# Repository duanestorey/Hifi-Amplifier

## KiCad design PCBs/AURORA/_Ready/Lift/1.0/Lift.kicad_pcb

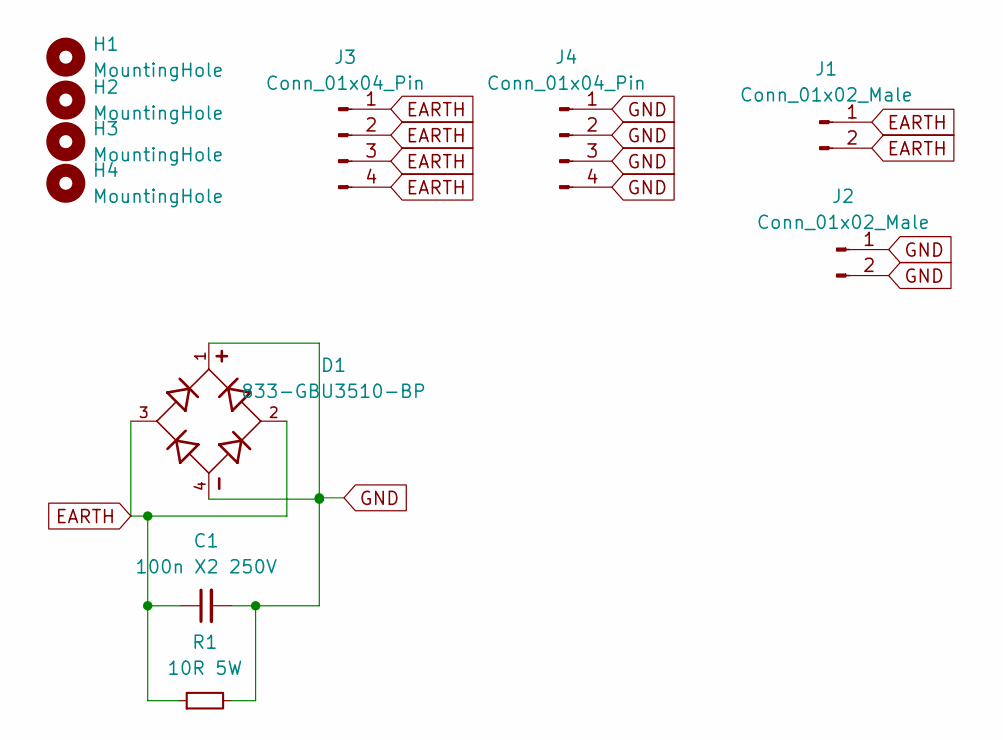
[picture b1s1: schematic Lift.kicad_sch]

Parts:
C1: 100n X2 250V; C_Rect_L18.0mm_W5.0mm_P15.00mm_FKS3_FKP3; Mouser 871-B32922X2104K000
D1: 833-GBU3510-BP; Diode_Bridge_Vishay_GBU; Mouser 833-GBU3510-BP
H1, H2, H3, H4: MountingHole; MountingHole_3.2mm_M3_DIN965_Pad_TopOnly
J1, J2: Conn_01x02_Male; JST_VH_B2P-VH-B_1x02_P3.96mm_Vertical
J3, J4: Conn_01x04_Pin; TerminalBlock_Phoenix_PT-1,5-4-3.5-H_1x04_P3.50mm_Horizontal
R1: 10R 5W; R_Axial_DIN0617_L17.0mm_D6.0mm_P25.40mm_Horizontal; Mouser 594-AC05W10R00J

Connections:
EARTH: C1.1, D1.2, D1.3, J1.1, J1.2, J3.1, J3.2, J3.3, J3.4, R1.1
GND: C1.2, D1.1, D1.4, J2.1, J2.2, J4.1, J4.2, J4.3, J4.4, R1.2

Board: 2 copper layers, 11 parts (0 on the bottom side), 2 nets, no tracks yet.

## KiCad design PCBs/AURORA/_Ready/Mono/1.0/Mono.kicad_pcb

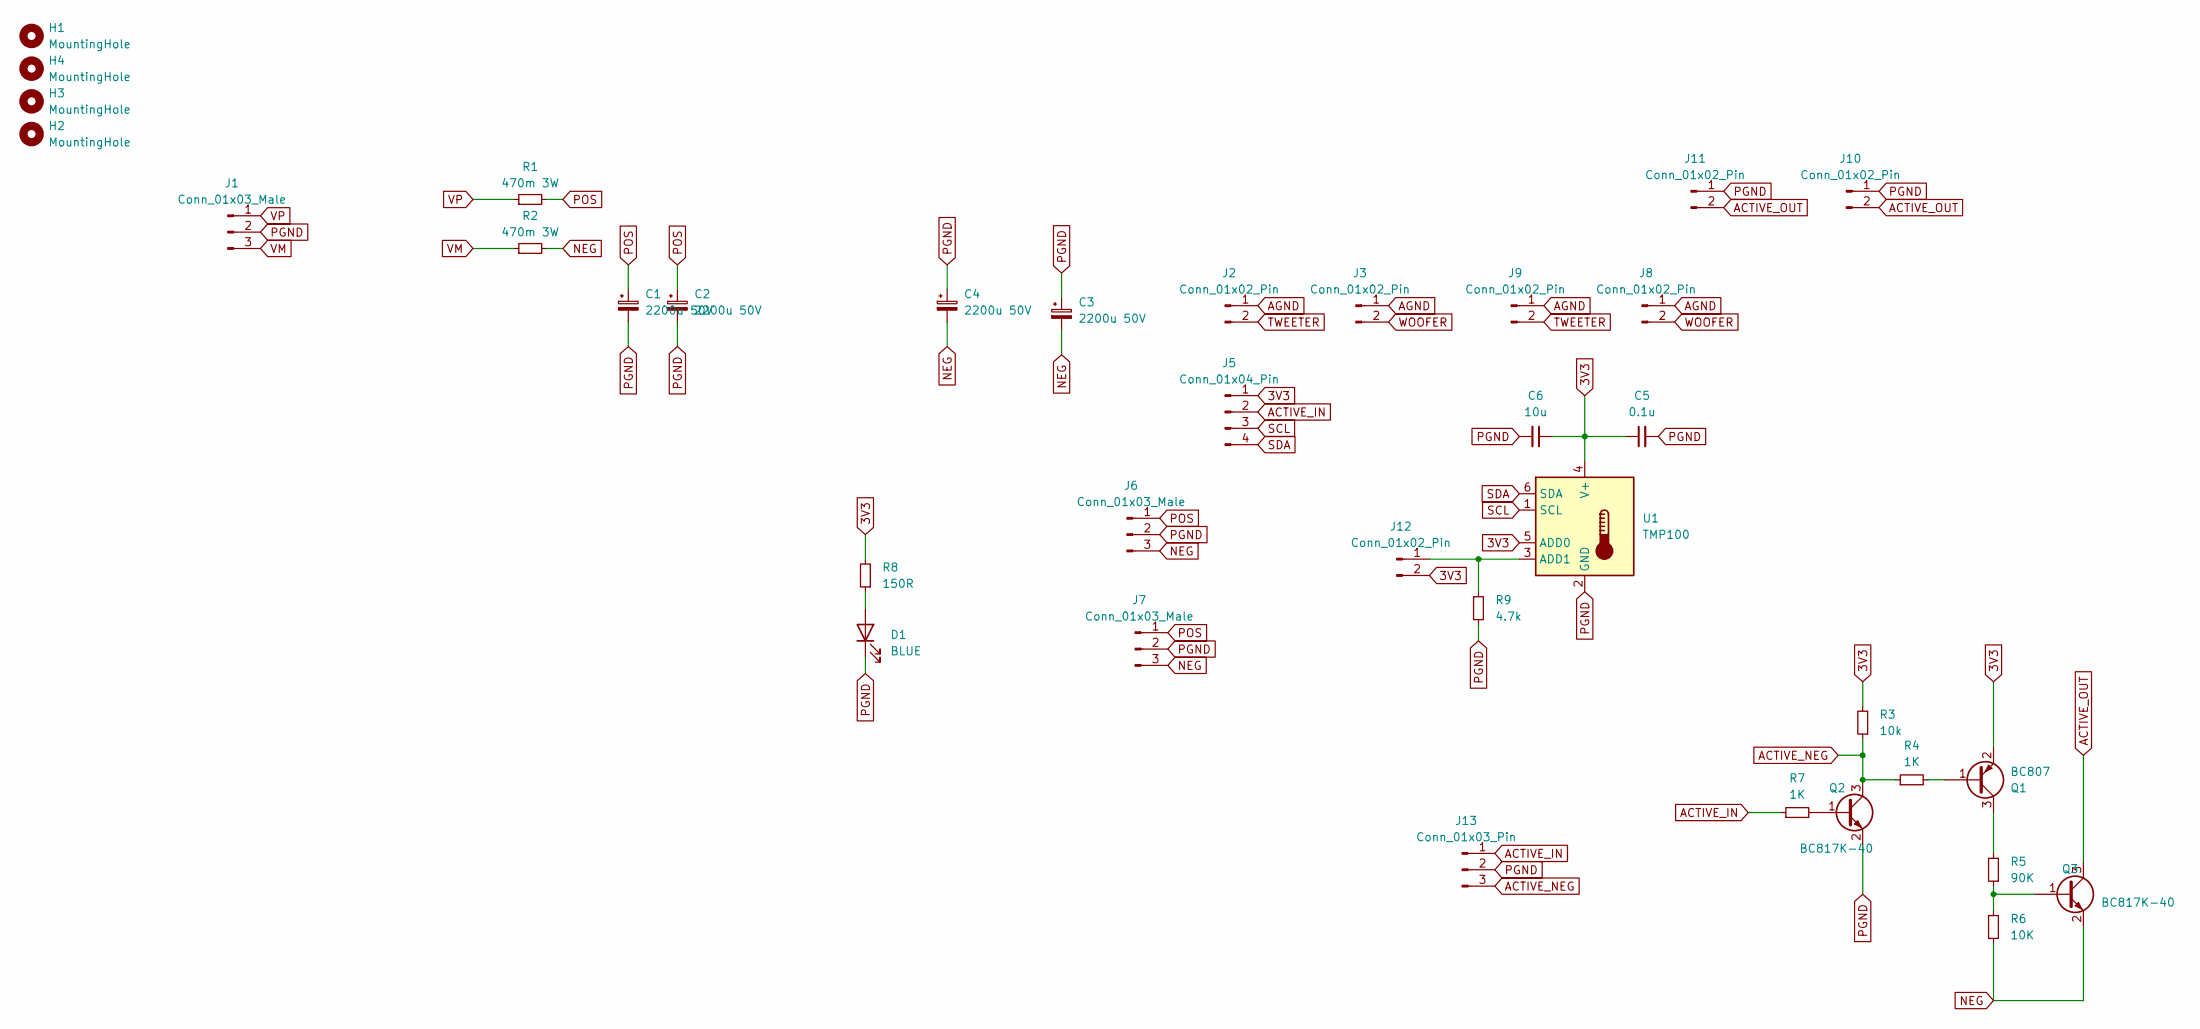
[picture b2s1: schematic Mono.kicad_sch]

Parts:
C1, C2, C3, C4: 2200u 50V; CP_Radial_D16.0mm_P7.50mm; Mouser 80-ESH228M050AM3AA
C5: 0.1u; C_0805_2012Metric_Pad1.18x1.45mm_HandSolder
C6: 10u; C_1206_3216Metric_Pad1.33x1.80mm_HandSolder
D1: BLUE; LED_0603_1608Metric_Pad1.05x0.95mm_HandSolder
H1, H2, H3, H4: MountingHole; MountingHole_3.2mm_M3_DIN965_Pad_TopOnly
J1, J6, J7: Conn_01x03_Male; JST_VH_B3P-VH-B_1x03_P3.96mm_Vertical
J2, J3, J8, J9, J10, J11: Conn_01x02_Pin; JST_PH_B2B-PH-K_1x02_P2.00mm_Vertical
J5: Conn_01x04_Pin; JST_PH_B4B-PH-K_1x04_P2.00mm_Vertical
J12: Conn_01x02_Pin; PinHeader_1x02_P2.54mm_Vertical
J13: Conn_01x03_Pin; JST_PH_B3B-PH-K_1x03_P2.00mm_Vertical
Q1: BC807; TSOT-23; Mouser 637-BC807-16
Q2, Q3: BC817K-40; TSOT-23; Mouser 637-BC817K-40
R1, R2: 470m 3W; R_1218_3246Metric_Pad1.22x4.75mm_HandSolder; Mouser RLW73PA3FR47TDF
R3: 10k; R_0603_1608Metric_Pad0.98x0.95mm_HandSolder
R4, R7: 1K; R_0603_1608Metric_Pad0.98x0.95mm_HandSolder
R5: 90K; R_0603_1608Metric_Pad0.98x0.95mm_HandSolder
R6: 10K; R_0603_1608Metric_Pad0.98x0.95mm_HandSolder
R8: 150R; R_0603_1608Metric_Pad0.98x0.95mm_HandSolder
R9: 4.7k; R_0603_1608Metric_Pad0.98x0.95mm_HandSolder
U1: TMP100; SOT-23-6

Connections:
3V3: C5.1, C6.1, J5.1, J12.2, Q1.2 (E), R3.2, R8.2, U1.4 (V+), U1.5 (ADD0)
ACTIVE_IN: J5.2, J13.1, R7.1
ACTIVE_NEG: J13.3, Q2.3 (C), R3.1, R4.1
ACTIVE_OUT: J10.2, J11.2, Q3.3 (C)
AGND: J2.1, J3.1, J8.1, J9.1
NEG: C3.2, C4.2, J6.3, J7.3, Q3.2 (E), R2.2, R6.1
unnamed: D1.2 (A), R8.1
unnamed: J12.1, R9.1, U1.3 (ADD1)
unnamed: Q1.1 (B), R4.2
unnamed: Q1.3 (C), R5.2
unnamed: Q2.1 (B), R7.2
unnamed: Q3.1 (B), R5.1, R6.2
PGND: C1.2, C2.2, C3.1, C4.1, C5.2, C6.2, D1.1 (K), J1.2, J6.2, J7.2, J10.1, J11.1, J13.2, Q2.2 (E), R9.2, U1.2 (GND)
POS: C1.1, C2.1, J6.1, J7.1, R1.2
SCL: J5.3, U1.1 (SCL)
SDA: J5.4, U1.6 (SDA)
TWEETER: J2.2, J9.2
VM: J1.3, R2.1
VP: J1.1, R1.1
WOOFER: J3.2, J8.2

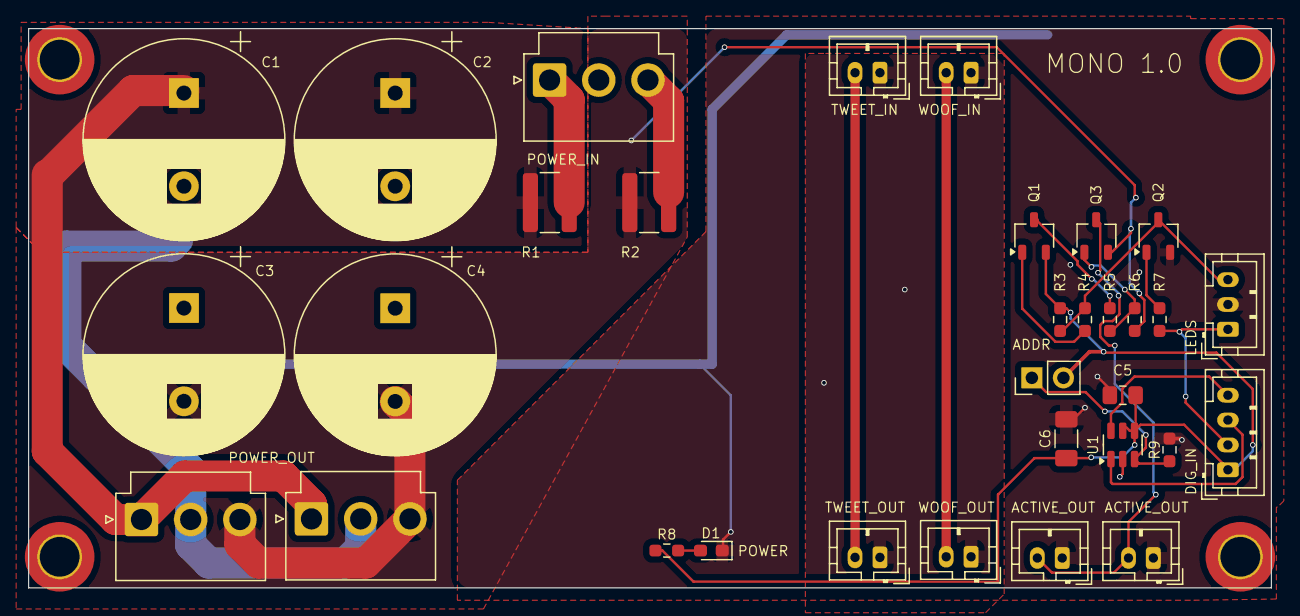
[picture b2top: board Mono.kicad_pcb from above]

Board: 2 copper layers, 100.0 x 45.0 mm, 36 parts (0 on the bottom side), 20 nets.

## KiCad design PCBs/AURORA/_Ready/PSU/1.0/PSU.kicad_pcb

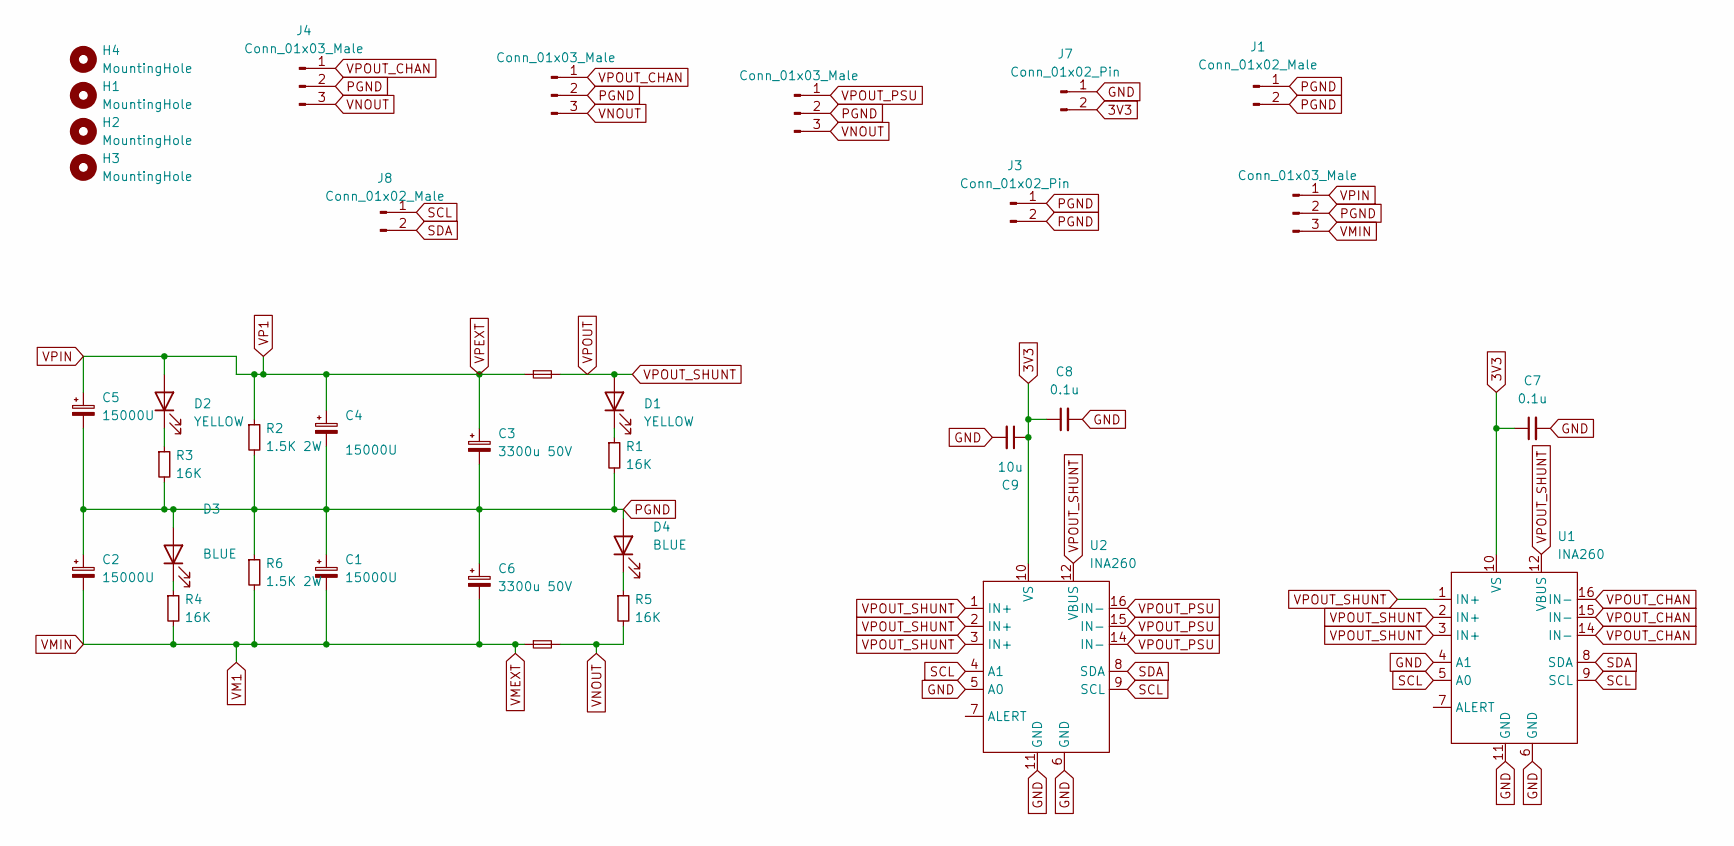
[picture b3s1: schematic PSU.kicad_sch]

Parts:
C1, C2, C4, C5: 15000U; CP_Radial_D30.0mm_P10.00mm_SnapIn
C3, C6: 3300u 50V; CP_Radial_D18.0mm_P7.50mm
C7, C8: 0.1u; C_0805_2012Metric_Pad1.18x1.45mm_HandSolder
C9: 10u; C_1206_3216Metric_Pad1.33x1.80mm_HandSolder
D1, D2: YELLOW; LED_0603_1608Metric_Pad1.05x0.95mm_HandSolder
D3, D4: BLUE; LED_0603_1608Metric_Pad1.05x0.95mm_HandSolder
F1, F2: Fuse_Small; Aliexpress Fuse 5x20
H1, H2, H3, H4: MountingHole; MountingHole_3mm_Pad_TopOnly
J1: Conn_01x02_Male; JST_VH_B2P-VH-B_1x02_P3.96mm_Vertical
J2, J4, J5, J6: Conn_01x03_Male; JST_VH_B3P-VH_1x03_P3.96mm_Vertical
J3, J7: Conn_01x02_Pin; JST_PH_B2B-PH-K_1x02_P2.00mm_Vertical
J8: Conn_01x02_Male; JST_PH_B2B-PH-K_1x02_P2.00mm_Vertical
R1, R3, R4, R5: 16K; LED_0603_1608Metric_Pad1.05x0.95mm_HandSolder; Mouser 71-CRCW060316K0FKEAC
R2, R6: 1.5K 2W; R_2512_6332Metric_Pad1.40x3.35mm_HandSolder; Mouser 652-CRM2512JW152ELF
U1, U2: INA260; TSSOP-16_4.4x5mm_P0.65mm; Mouser 595-INA260AIPWR

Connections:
3V3: C7.1, C8.1, C9.1, J7.2, U1.10 (VS), U2.10 (VS)
GND: C7.2, C8.2, C9.2, J7.1, U1.4 (A1), U1.6 (GND), U1.11 (GND), U2.5 (A0), U2.6 (GND), U2.11 (GND)
unnamed: D1.1 (K), R1.1
unnamed: D2.1 (K), R3.1
unnamed: D3.1 (K), R4.1
unnamed: D4.1 (K), R5.1
PGND: C1.1, C2.1, C3.2, C4.2, C5.2, C6.1, D3.2 (A), D4.2 (A), J1.1, J1.2, J2.2, J3.1, J3.2, J4.2, J5.2, J6.2, R1.2, R2.2, R3.2, R6.1
SCL: J8.1, U1.5 (A0), U1.9 (SCL), U2.4 (A1), U2.9 (SCL)
SDA: J8.2, U1.8 (SDA), U2.8 (SDA)
VM1: C1.2, C2.2, C6.2, F2.1, J2.3, R4.2, R6.2
VNOUT: F2.2, J4.3, J5.3, J6.3, R5.2
VP1: C3.1, C4.1, C5.1, D2.2 (A), F1.1, J2.1, R2.1
VPOUT: D1.2 (A), F1.2, U1.1 (IN+), U1.2 (IN+), U1.3 (IN+), U1.12 (VBUS), U2.1 (IN+), U2.2 (IN+), U2.3 (IN+), U2.12 (VBUS)
VPOUT_CHAN: J4.1, J5.1, U1.14 (IN-), U1.15 (IN-), U1.16 (IN-)
VPOUT_PSU: J6.1, U2.14 (IN-), U2.15 (IN-), U2.16 (IN-)

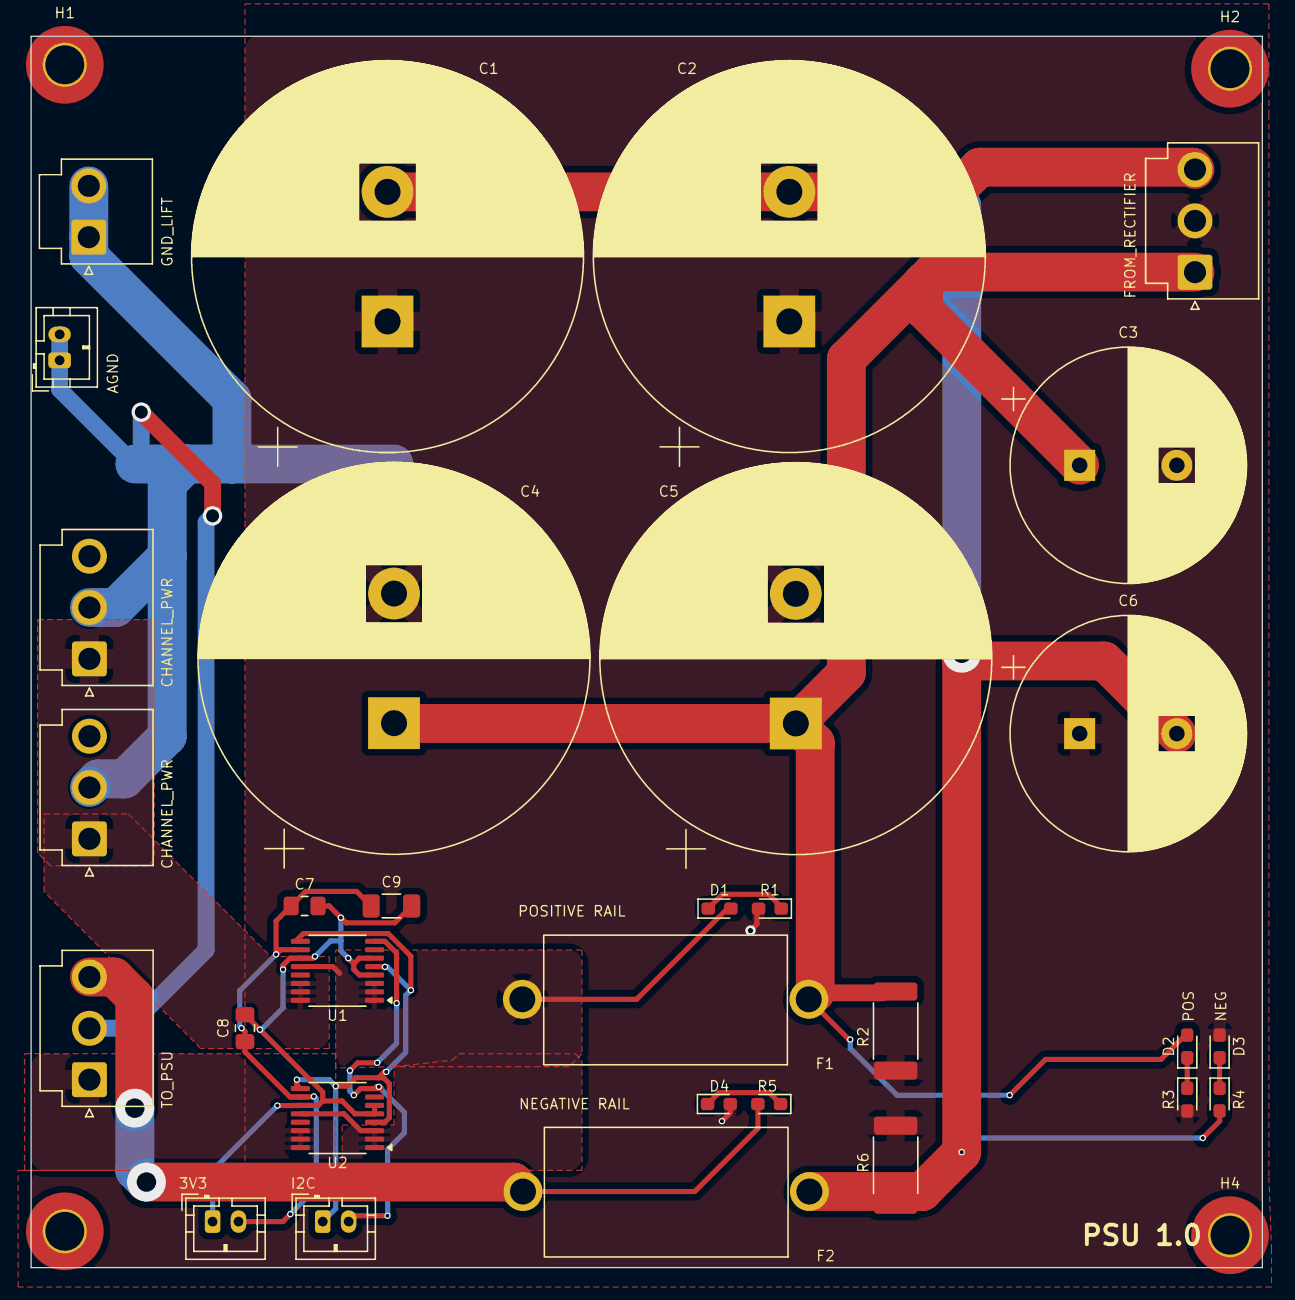
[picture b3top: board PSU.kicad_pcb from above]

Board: 2 copper layers, 95.0 x 95.0 mm, 35 parts (0 on the bottom side), 15 nets.

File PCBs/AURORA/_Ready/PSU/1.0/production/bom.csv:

Designator,Footprint,Quantity,Value,LCSC Part #
"C1, C2, C4, C5",CP_Radial_D30.0mm_P10.00mm_SnapIn,4,15000U,
"C3, C6",CP_Radial_D18.0mm_P7.50mm,2,3300u 50V,
"C7, C8",0805,2,0.1u,
C9,1206,1,10u,
"D1, D2",0603,2,YELLOW,
"D3, D4",0603,2,BLUE,
"F1, F2",Aliexpress Fuse 5x20,2,Fuse_Small,
"H1, H2, H3, H4",MountingHole_3mm_Pad_TopOnly,4,MountingHole,
J1,JST_VH_B2P-VH-B_1x02_P3.96mm_Vertical,1,Conn_01x02_Male,
"J2, J4, J5, J6",JST_VH_B3P-VH_1x03_P3.96mm_Vertical,4,Conn_01x03_Male,
"J3, J7",JST_PH_B2B-PH-K_1x02_P2.00mm_Vertical,2,Conn_01x02_Pin,
J8,JST_PH_B2B-PH-K_1x02_P2.00mm_Vertical,1,Conn_01x02_Male,
"R1, R3, R4, R5",0603,4,16K,
"R2, R6",2512,2,1.5K 2W,
"U1, U2",TSSOP-16_4.4x5mm_P0.65mm,2,INA260,

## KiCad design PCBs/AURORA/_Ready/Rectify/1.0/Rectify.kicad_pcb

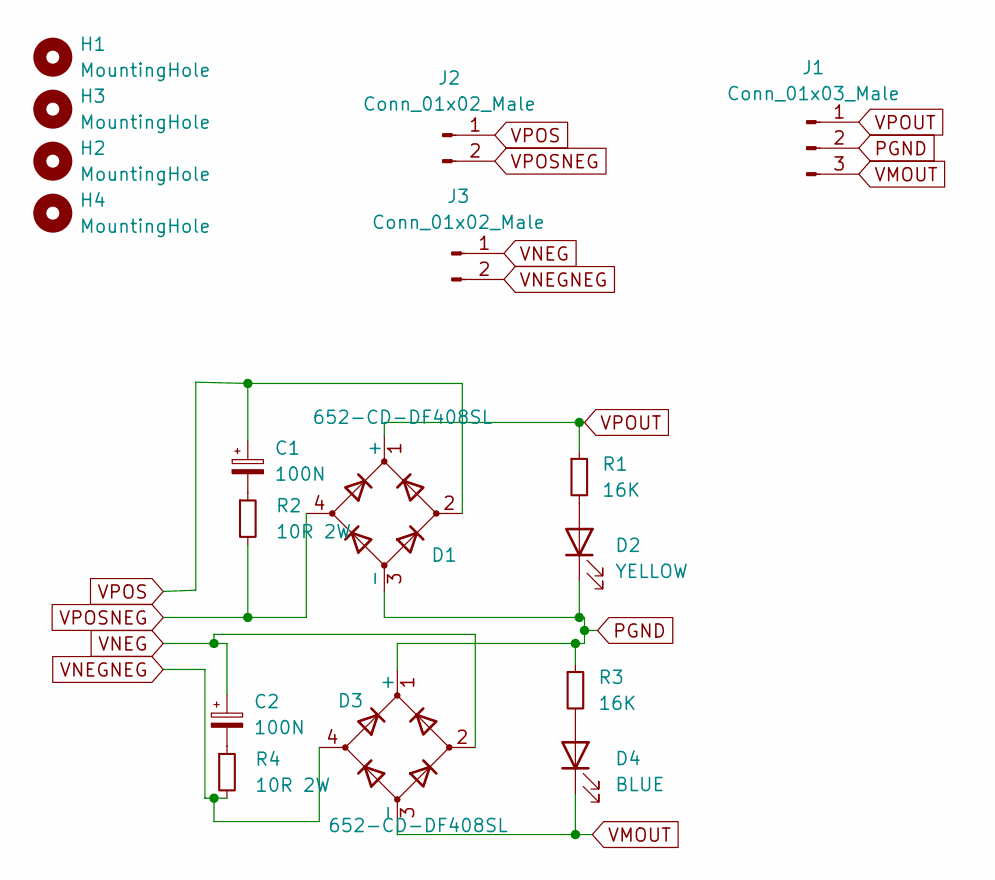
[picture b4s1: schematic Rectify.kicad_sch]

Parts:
C1, C2: 100N; C_Rect_L13.0mm_W6.0mm_P10.00mm_FKS3_FKP3_MKS4; Mouser 505-MKP1D031003G00JS
D1, D3: 652-CD-DF408SL; Diode_Bridge_Bourns_CD-DF4xxS; Mouser 652-CD-DF408SL
D2: YELLOW; LED_0603_1608Metric_Pad1.05x0.95mm_HandSolder
D4: BLUE; LED_0603_1608Metric_Pad1.05x0.95mm_HandSolder
H1, H2, H3, H4: MountingHole; MountingHole_3.2mm_M3_Pad_TopOnly
J1: Conn_01x03_Male; JST_VH_B3P-VH_1x03_P3.96mm_Vertical
J2, J3: Conn_01x02_Male; JST_VH_B2P-VH-B_1x02_P3.96mm_Vertical
R1, R3: 16K; R_0603_1608Metric_Pad0.98x0.95mm_HandSolder
R2, R4: 10R 2W; R_2512_6332Metric; Mouser 603-SR2512JK-7W10RL

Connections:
unnamed: C1.2, R2.1
unnamed: C2.2, R4.1
unnamed: D2.2 (A), R1.2
unnamed: D4.2 (A), R3.2
PGND: D1.3 (-), D2.1 (K), D3.1 (+), J1.2, R3.1
VMOUT: D3.3 (-), D4.1 (K), J1.3
VNEG: C2.1, D3.2, J3.1
VNEGNEG: D3.4, J3.2, R4.2
VPOS: C1.1, D1.2, J2.1
VPOSNEG: D1.4, J2.2, R2.2
VPOUT: D1.1 (+), J1.1, R1.1

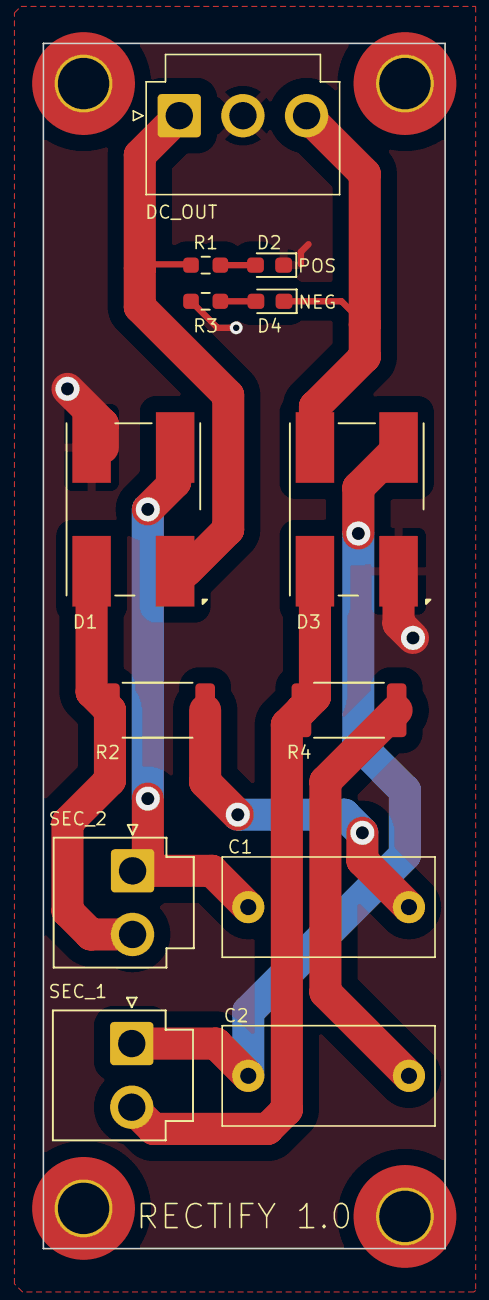
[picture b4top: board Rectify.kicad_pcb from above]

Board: 2 copper layers, 25.0 x 75.0 mm, 17 parts (0 on the bottom side), 11 nets.

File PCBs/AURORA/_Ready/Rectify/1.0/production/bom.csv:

Designator,Footprint,Quantity,Value,LCSC Part #
"C1, C2",C_Rect_L13.0mm_W6.0mm_P10.00mm_FKS3_FKP3_MKS4,2,100N,
"D1, D3",Diode_Bridge_Bourns_CD-DF4xxS,2,652-CD-DF408SL,
D2,0603,1,YELLOW,
D4,0603,1,BLUE,
"H1, H2, H3, H4",MountingHole_3.2mm_M3_Pad_TopOnly,4,MountingHole,
J1,JST_VH_B3P-VH_1x03_P3.96mm_Vertical,1,Conn_01x03_Male,
"J2, J3",JST_VH_B2P-VH-B_1x02_P3.96mm_Vertical,2,Conn_01x02_Male,
"R1, R3",0603,2,16K,
"R2, R4",2512,2,10R 2W,

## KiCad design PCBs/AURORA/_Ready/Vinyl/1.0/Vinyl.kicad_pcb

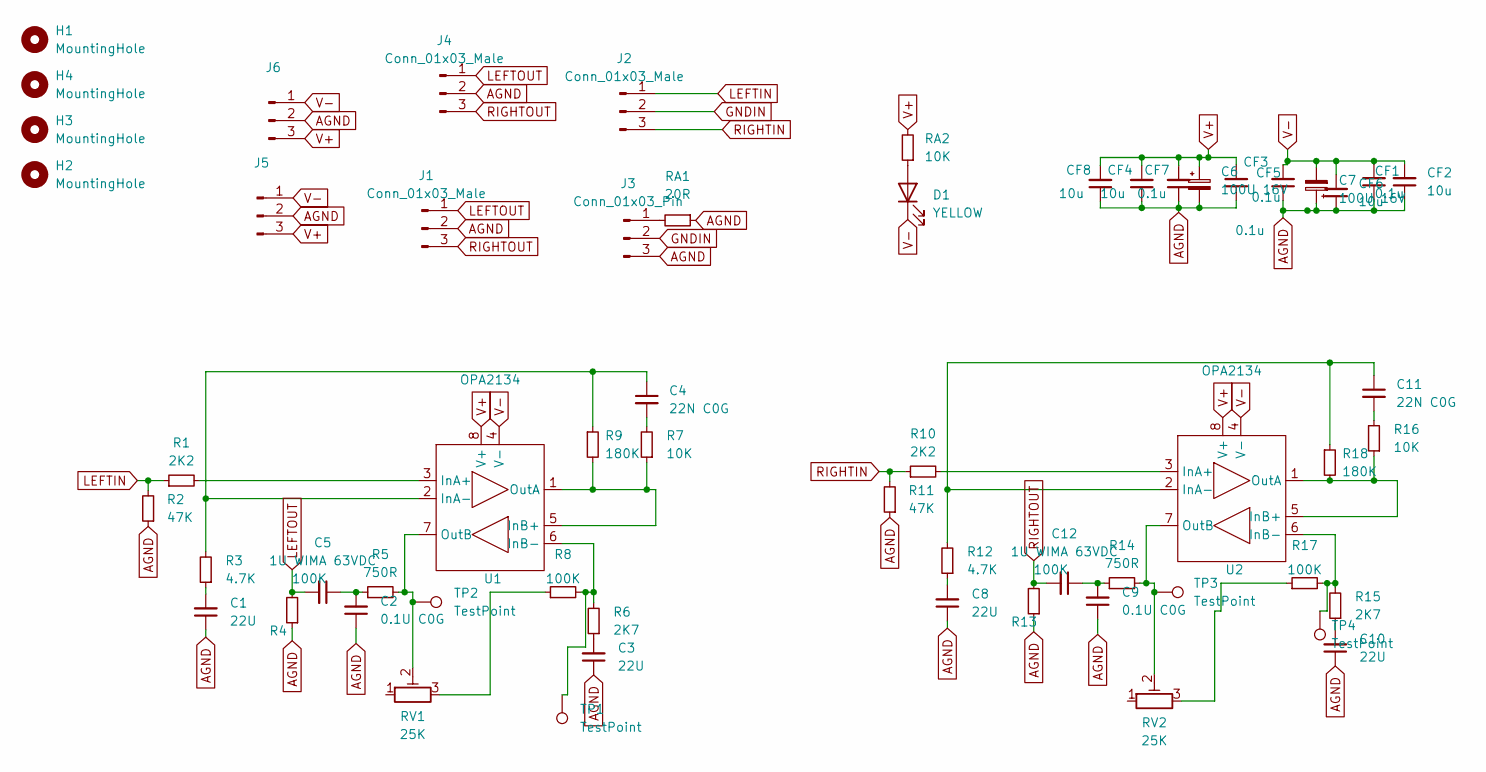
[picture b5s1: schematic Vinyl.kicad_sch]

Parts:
C1, C3, C8, C10: 22U; CP_Radial_D6.3mm_P2.50mm
C2, C9: 0.1U C0G; C_1206_3216Metric_Pad1.33x1.80mm_HandSolder
C4, C11: 22N C0G; C_0805_2012Metric_Pad1.18x1.45mm_HandSolder
C5, C12: 1U WIMA 63VDC; C_Rect_L7.2mm_W11.0mm_P5.00mm_FKS2_FKP2_MKS2_MKP2; Mouser 505-MKP2C0411NMN
C6, C7: 100U 16V; CP_Radial_D6.3mm_P2.50mm
CF1, CF3, CF5, CF7: 0.1u; C_0805_2012Metric_Pad1.18x1.45mm_HandSolder
CF2, CF4, CF6, CF8: 10u; C_1206_3216Metric_Pad1.33x1.80mm_HandSolder
D1: YELLOW; LED_0603_1608Metric_Pad1.05x0.95mm_HandSolder
H1, H2, H3, H4: MountingHole; MountingHole_3.2mm_M3_DIN965_Pad_TopOnly
J1, J2, J5, J6: Conn_01x03_Male; JST_PH_B3B-PH-K_1x03_P2.00mm_Vertical
J3: Conn_01x03_Pin; PinHeader_1x03_P2.54mm_Vertical
J4: Conn_01x03_Male; PinHeader_1x03_P2.54mm_Vertical
R1, R10: 2K2; R_0805_2012Metric_Pad1.20x1.40mm_HandSolder
R2, R11: 47K; R_0805_2012Metric_Pad1.20x1.40mm_HandSolder
R3, R12: 4.7K; R_0805_2012Metric_Pad1.20x1.40mm_HandSolder
R4, R8, R13, R17: 100K; R_0805_2012Metric_Pad1.20x1.40mm_HandSolder
R5, R14: 750R; R_0805_2012Metric_Pad1.20x1.40mm_HandSolder
R6, R15: 2K7; R_0805_2012Metric_Pad1.20x1.40mm_HandSolder
R7, R16: 10K; R_0805_2012Metric_Pad1.20x1.40mm_HandSolder
R9, R18: 180K; R_0805_2012Metric_Pad1.20x1.40mm_HandSolder
RA1: 20R; R_0603_1608Metric
RA2: 10K; R_0603_1608Metric
RV1, RV2: 25K; Potentiometer_Bourns_3296W_Vertical
TP1, TP2, TP3, TP4: TestPoint; TestPoint_THTPad_1.5x1.5mm_Drill0.7mm
U1, U2: OPA2134; DIP-8_W7.62mm_Socket

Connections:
AGND: C1.1, C2.1, C3.1, C6.2, C7.1, C8.1, C9.1, C10.1, CF1.1, CF2.1, CF3.1, CF4.1, CF5.1, CF6.1, CF7.1, CF8.1, J1.2, J3.3, J4.2, J5.2, J6.2, R2.1, R4.1, R11.1, R13.1, RA1.1
GNDIN: J2.2, J3.2
LEFTIN: J2.1, R1.1, R2.2
LEFTOUT: C5.2, J1.1, J4.1, R4.2
unnamed: C1.2, R3.1
unnamed: C2.2, C5.1, R5.1
unnamed: C3.2, R6.1
unnamed: C4.2, R7.2
unnamed: C8.2, R12.1
unnamed: C10.2, R15.1
unnamed: C11.2, R16.2
unnamed: C9.2, C12.1, R14.1
unnamed: D1.2 (A), RA2.1
unnamed: J3.1, RA1.2
unnamed: R8.1, RV1.3
unnamed: R17.1, RV2.3
unnamed: R1.2, U1.3 (InA+)
unnamed: C4.1, R3.2, R9.1, U1.2 (InA-)
unnamed: R7.1, R9.2, U1.1 (OutA), U1.5 (InB+)
unnamed: R6.2, R8.2, TP1.1, U1.6 (InB-)
unnamed: R5.2, RV1.2, TP2.1, U1.7 (OutB)
unnamed: R10.2, U2.3 (InA+)
unnamed: C11.1, R12.2, R18.1, U2.2 (InA-)
unnamed: R16.1, R18.2, U2.1 (OutA), U2.5 (InB+)
unnamed: R15.2, R17.2, TP4.1, U2.6 (InB-)
unnamed: R14.2, RV2.2, TP3.1, U2.7 (OutB)
RIGHTIN: J2.3, R10.1, R11.2
RIGHTOUT: C12.2, J1.3, J4.3, R13.2
V+: C6.1, CF3.2, CF4.2, CF7.2, CF8.2, J5.3, J6.3, RA2.2, U1.8 (V+), U2.8 (V+)
V-: C7.2, CF1.2, CF2.2, CF5.2, CF6.2, D1.1 (K), J5.1, J6.1, U1.4 (V-), U2.4 (V-)

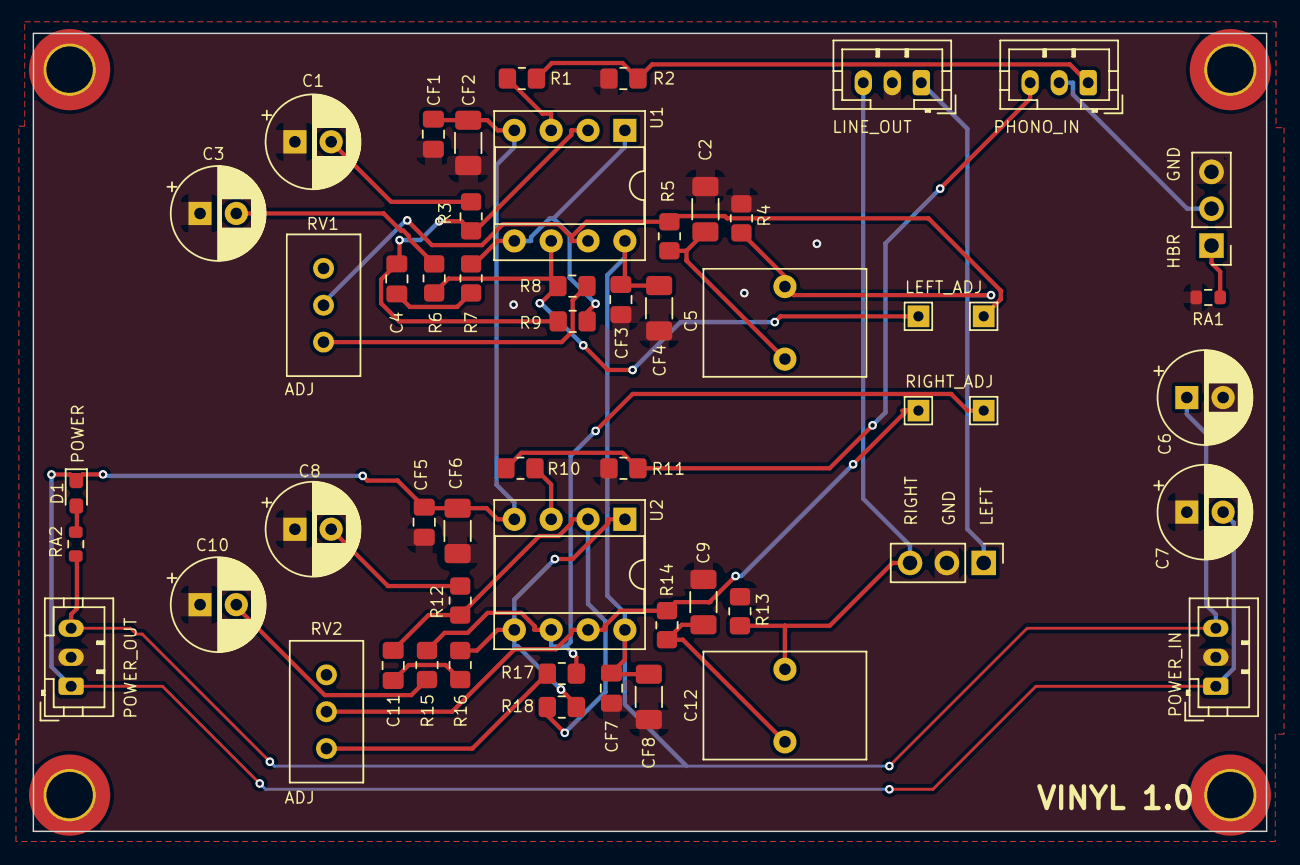
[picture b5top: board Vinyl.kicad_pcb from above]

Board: 2 copper layers, 85.0 x 55.0 mm, 59 parts (0 on the bottom side), 30 nets.

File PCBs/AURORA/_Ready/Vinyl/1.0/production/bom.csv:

Designator,Footprint,Quantity,Value,LCSC Part #
"C1, C10, C3, C8",CP_Radial_D6.3mm_P2.50mm,4,22U,
"C11, C4",0805,2,22N C0G,
"C12, C5",C_Rect_L7.2mm_W11.0mm_P5.00mm_FKS2_FKP2_MKS2_MKP2,2,1U WIMA 63VDC,
"C2, C9",1206,2,0.1U C0G,
"C6, C7",CP_Radial_D6.3mm_P2.50mm,2,100U 16V,
"CF1, CF3, CF5, CF7",0805,4,0.1u,
"CF2, CF4, CF6, CF8",1206,4,10u,
D1,0603,1,YELLOW,
"H1, H2, H3, H4",MountingHole_3.2mm_M3_DIN965_Pad_TopOnly,4,MountingHole,
"J1, J2, J5, J6",JST_PH_B3B-PH-K_1x03_P2.00mm_Vertical,4,Conn_01x03_Male,
J3,PinHeader_1x03_P2.54mm_Vertical,1,Conn_01x03_Pin,
J4,PinHeader_1x03_P2.54mm_Vertical,1,Conn_01x03_Male,
"R1, R10",0805,2,2K2,
"R11, R2",0805,2,47K,
"R12, R3",0805,2,4.7K,
"R13, R17, R4, R8",0805,4,100K,
"R14, R5",0805,2,750R,
"R15, R6",0805,2,2K7,
"R16, R7",0805,2,10K,
"R18, R9",0805,2,180K,
RA1,0603,1,20R,
RA2,0603,1,10K,
"RV1, RV2",Potentiometer_Bourns_3296W_Vertical,2,25K,
"TP1, TP2, TP3, TP4",TestPoint_THTPad_1.5x1.5mm_Drill0.7mm,4,TestPoint,
"U1, U2",DIP-8_W7.62mm_Socket,2,OPA2134,

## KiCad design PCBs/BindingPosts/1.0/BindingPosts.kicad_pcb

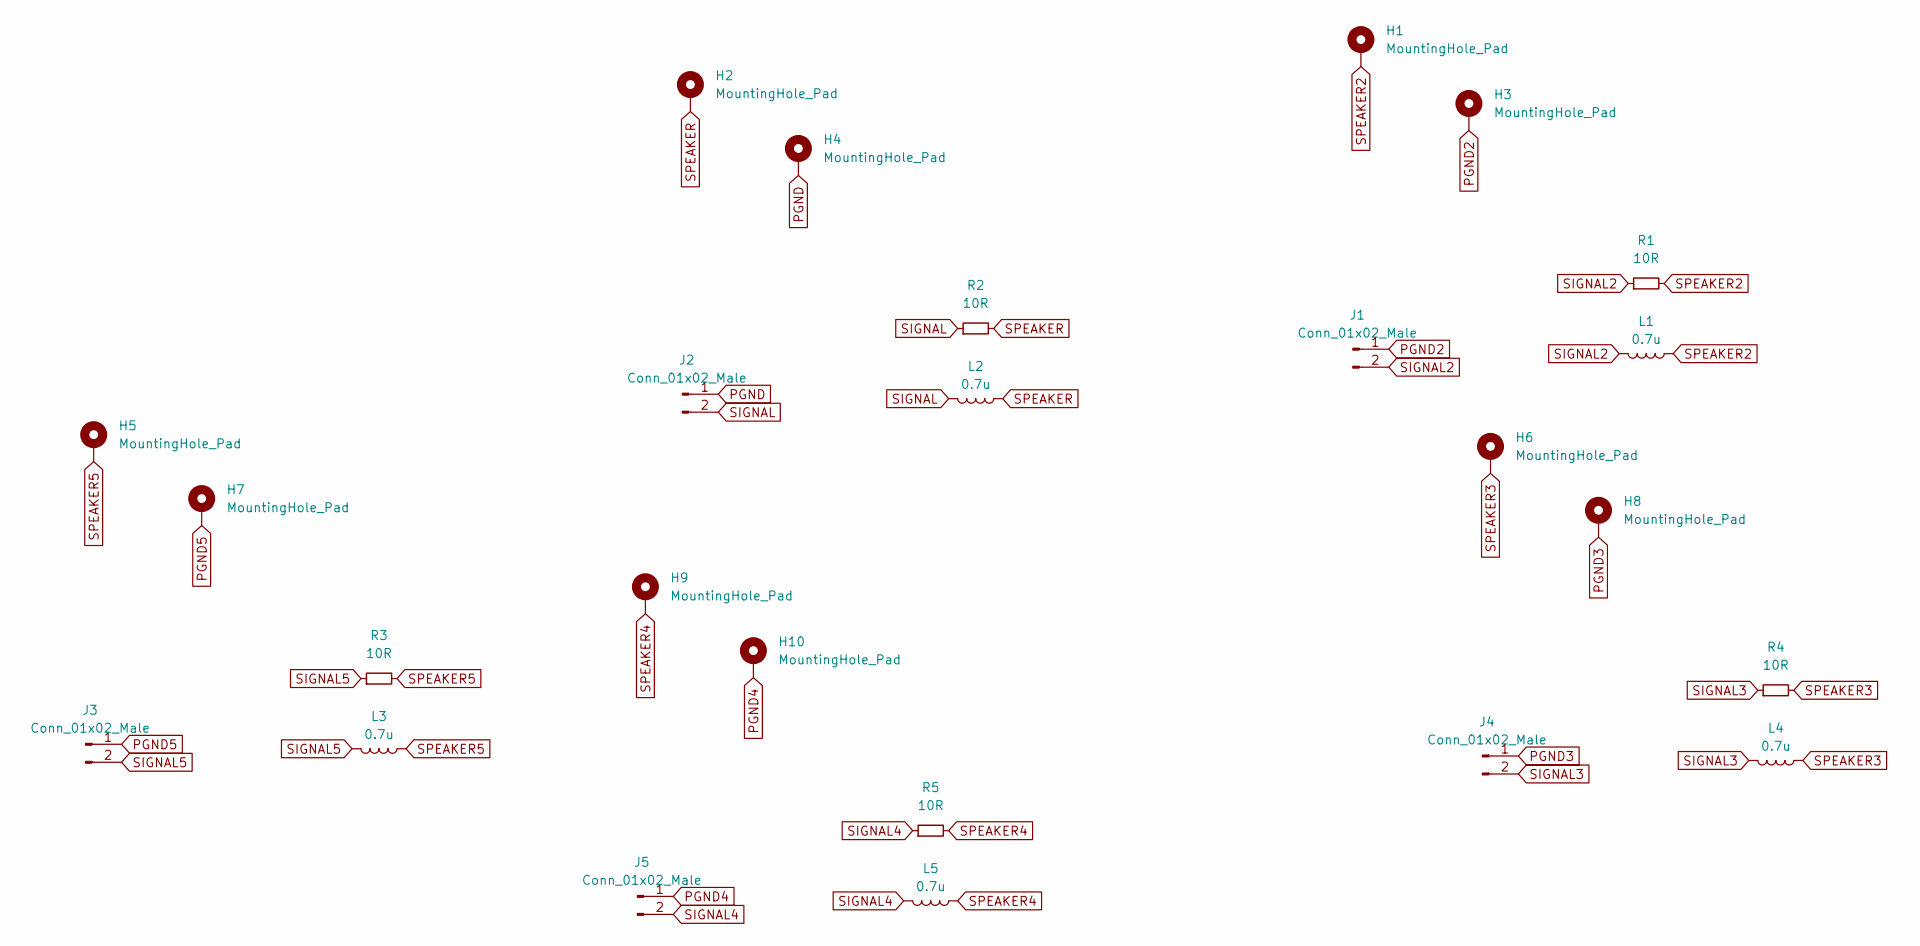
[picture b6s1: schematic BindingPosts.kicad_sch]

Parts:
H1, H2, H3, H4, H5, H6, H7, H8, H9, H10: MountingHole_Pad; MountingHole_4.3mm_M4_DIN965_Pad
J1, J2, J3, J4, J5: Conn_01x02_Male; JST_VH_B2P-VH-B_1x02_P3.96mm_Vertical
L1, L2, L3, L4, L5: 0.7u; L_Axial_L26.0mm_D10.0mm_P30.48mm_Horizontal_Fastron_77A
R1, R2, R3, R4, R5: 10R; R_Axial_Power_L25.0mm_W6.4mm_P27.94mm

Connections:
PGND: H4.1, J2.1
PGND2: H3.1, J1.1
PGND3: H8.1, J4.1
PGND4: H10.1, J5.1
PGND5: H7.1, J3.1
SIGNAL: J2.2, L2.2, R2.1
SIGNAL2: J1.2, L1.2, R1.1
SIGNAL3: J4.2, L4.2, R4.1
SIGNAL4: J5.2, L5.2, R5.1
SIGNAL5: J3.2, L3.2, R3.1
SPEAKER: H2.1, L2.1, R2.2
SPEAKER2: H1.1, L1.1, R1.2
SPEAKER3: H6.1, L4.1, R4.2
SPEAKER4: H9.1, L5.1, R5.2
SPEAKER5: H5.1, L3.1, R3.2

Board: 2 copper layers, 25 parts (0 on the bottom side), 15 nets, no tracks yet.

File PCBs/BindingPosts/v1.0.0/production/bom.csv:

Designator,Footprint,Quantity,Value,LCSC Part #
"H1, H10, H2, H3, H4, H5, H6, H7, H8, H9",MountingHole_4.3mm_M4_DIN965_Pad,10,MountingHole_Pad,
"J1, J2, J3, J4, J5",JST_VH_B2P-VH-B_1x02_P3.96mm_Vertical,5,Conn_01x02_Male,
"L1, L2, L3, L4, L5",L_Axial_L26.0mm_D10.0mm_P30.48mm_Horizontal_Fastron_77A,5,0.7u,
"R1, R2, R3, R4, R5",R_Axial_Power_L25.0mm_W6.4mm_P27.94mm,5,10R,
